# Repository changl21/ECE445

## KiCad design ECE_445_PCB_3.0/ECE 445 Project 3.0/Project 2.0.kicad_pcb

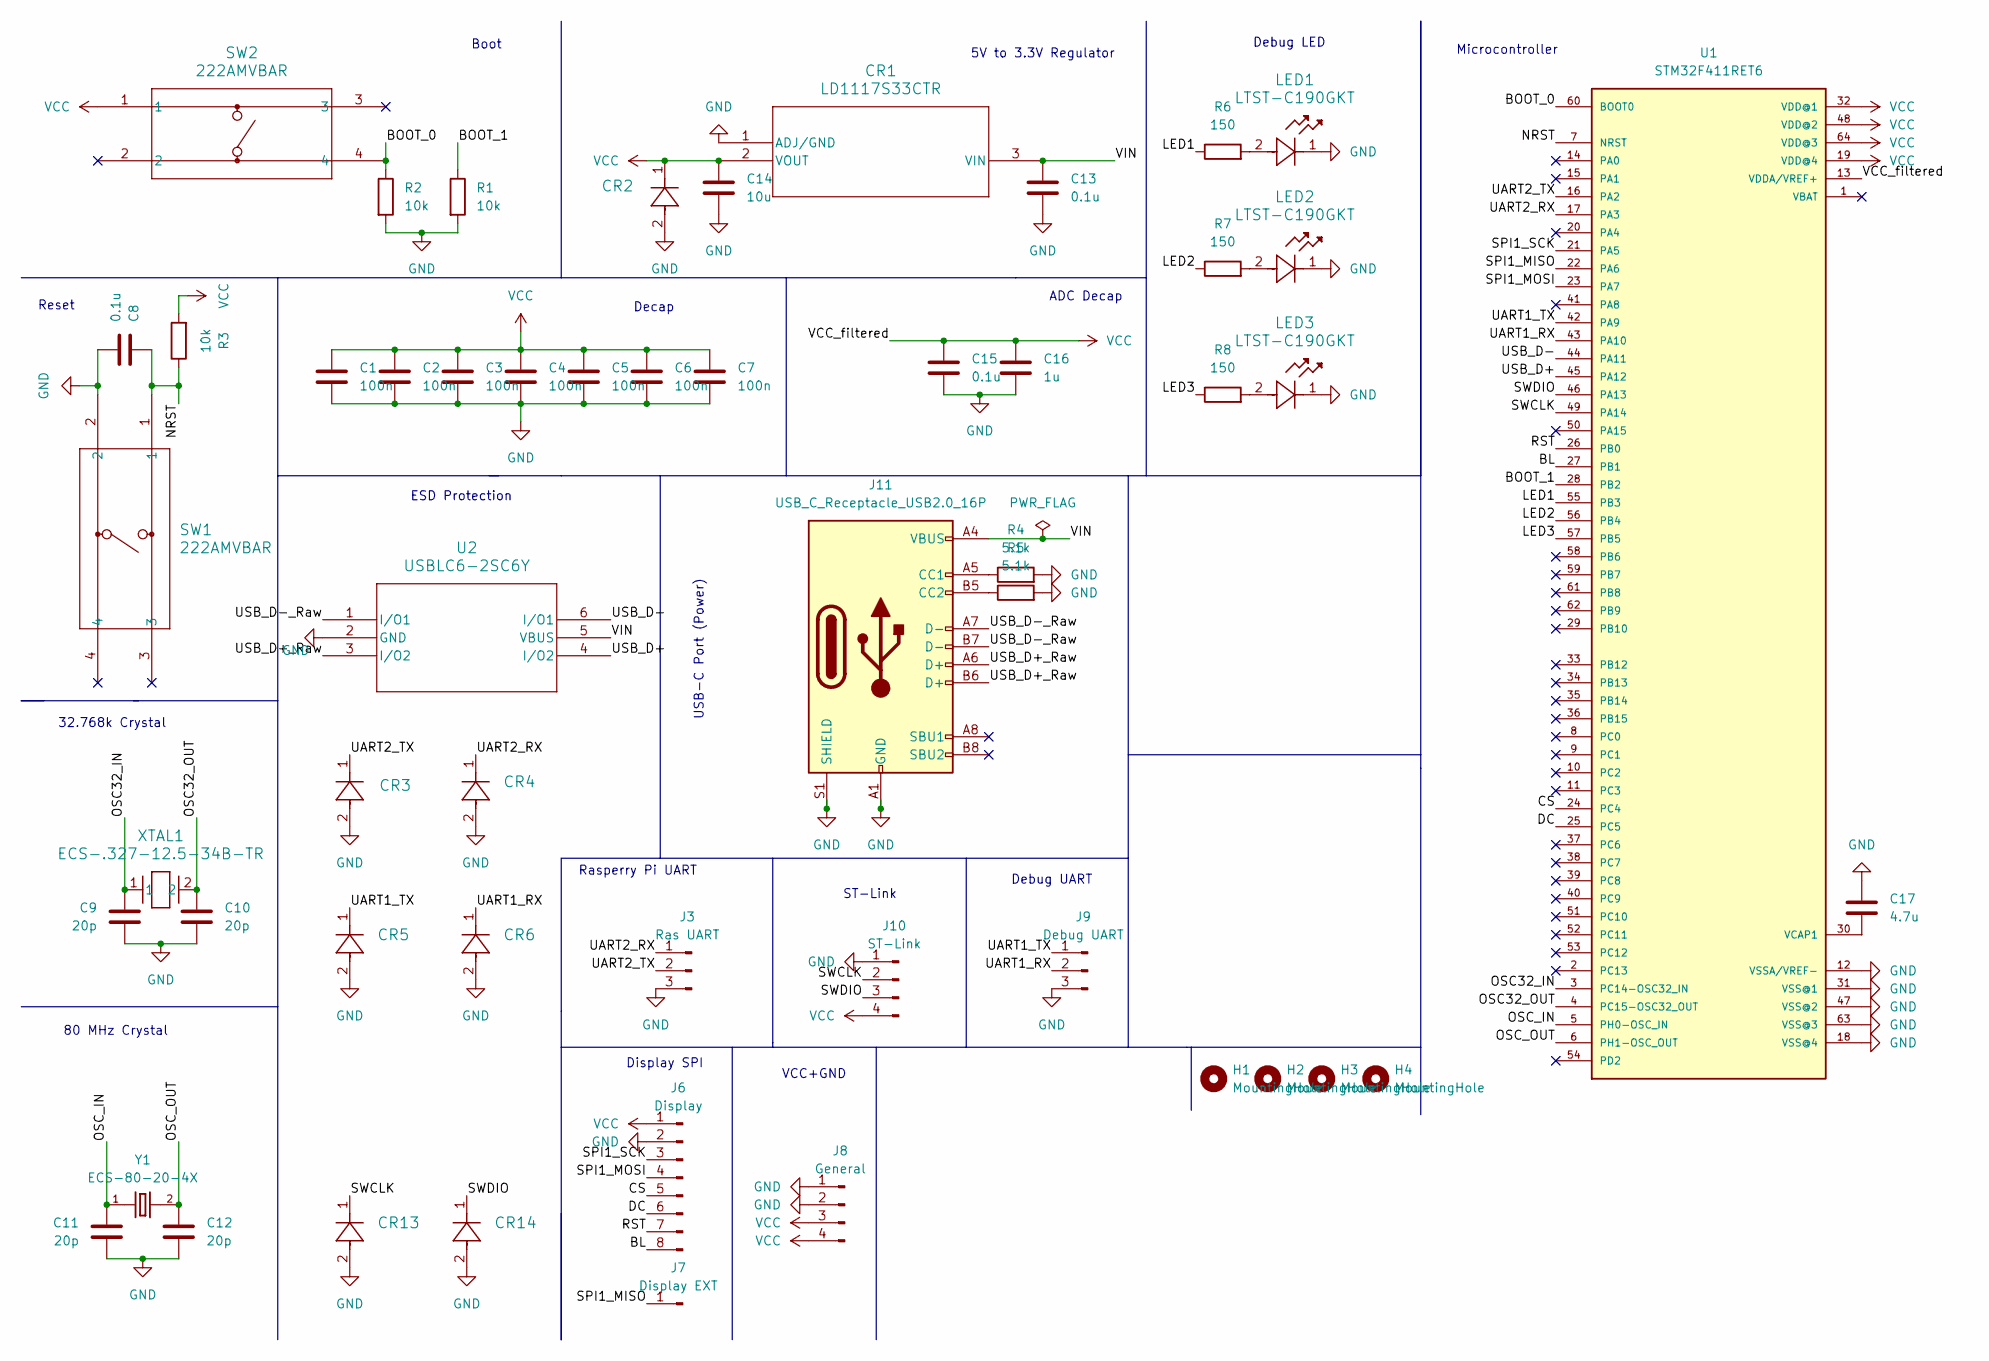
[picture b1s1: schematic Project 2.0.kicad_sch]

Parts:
C1, C2, C3, C4, C5, C6, C7: 100n; C_0603_1608Metric_Pad1.08x0.95mm_HandSolder
C8, C13, C15: 0.1u; C_0603_1608Metric_Pad1.08x0.95mm_HandSolder
C9, C10, C11, C12: 20p; C_0603_1608Metric_Pad1.08x0.95mm_HandSolder
C14: 10u; C_0805_2012Metric_Pad1.18x1.45mm_HandSolder
C16: 1u; C_0603_1608Metric_Pad1.08x0.95mm_HandSolder
C17: 4.7u; C_0603_1608Metric_Pad1.08x0.95mm_HandSolder
CR1: LD1117S33CTR; SOT-223_STM-L
CR2, CR3, CR4, CR5, CR6, CR13, CR14: PESD3V3L1BA_115; DIODE_PESD3V3L1BA_115_NEX-L
H1, H2, H3, H4: MountingHole; MountingHole_3.2mm_M3
J3: Ras UART; PinHeader_1x03_P2.54mm_Vertical
J6: Display; PinHeader_1x08_P2.54mm_Vertical
J7: Display EXT; PinHeader_1x01_P2.54mm_Vertical
J8: General; PinHeader_1x04_P2.54mm_Vertical
J9: Debug UART; PinHeader_1x03_P2.54mm_Vertical
J10: ST-Link; PinHeader_1x04_P2.54mm_Vertical
J11: USB_C_Receptacle_USB2.0_16P; USB_C_Receptacle_GCT_USB4105-xx-A_16P_TopMnt_Horizontal
LED1, LED2, LED3: LTST-C190GKT; LED_LTST-C190CKT_LTO
R1, R2, R3: 10k; R_0805_2012Metric_Pad1.20x1.40mm_HandSolder
R4, R5: 5.1k; R_0805_2012Metric_Pad1.20x1.40mm_HandSolder
R6, R7, R8: 150; R_0805_2012Metric_Pad1.20x1.40mm_HandSolder
SW1, SW2: 222AMVBAR; SO4_222A-M-V-B_CTS
U1: STM32F411RET6; QFP50P1200X1200X160-64N
U2: USBLC6-2SC6Y; SOT23-6L_STM-L
XTAL1: ECS-.327-12.5-34B-TR; XTAL_ECS-31B_ECS-L
Y1: ECS-80-20-4X; XTAL_ECS-80-20-4X

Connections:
/BL: J6.8, U1.27 (PB1)
/BOOT_0: R2.1, SW2.4, U1.60 (BOOT0)
/BOOT_1: R1.1, U1.28 (PB2)
/CS: J6.5, U1.24 (PC4)
/DC: J6.6, U1.25 (PC5)
/LED1: R6.1, U1.55 (PB3)
/LED2: R7.1, U1.56 (PB4)
/LED3: R8.1, U1.57 (PB5)
/NRST: C8.1, R3.1, SW1.1, U1.7 (NRST)
/OSC32_IN: C9.1, U1.3 (PC14-OSC32_IN), XTAL1.1
/OSC32_OUT: C10.1, U1.4 (PC15-OSC32_OUT), XTAL1.2
/OSC_IN: C11.1, U1.5 (PH0-OSC_IN), Y1.1
/OSC_OUT: C12.1, U1.6 (PH1-OSC_OUT), Y1.2
/RST: J6.7, U1.26 (PB0)
/SPI1_MISO: J7.1, U1.22 (PA6)
/SPI1_MOSI: J6.4, U1.23 (PA7)
/SPI1_SCK: J6.3, U1.21 (PA5)
/SWCLK: CR13.1, J10.2, U1.49 (PA14)
/SWDIO: CR14.1, J10.3, U1.46 (PA13)
/UART1_RX: CR6.1, J9.2, U1.43 (PA10)
/UART1_TX: CR5.1, J9.1, U1.42 (PA9)
/UART2_RX: CR4.1, J3.1, U1.17 (PA3)
/UART2_TX: CR3.1, J3.2, U1.16 (PA2)
/USB_D+: U1.45 (PA12), U2.4 (I/O2)
/USB_D+_Raw: J11.A6 (D+), J11.B6 (D+), U2.3 (I/O2)
/USB_D-: U1.44 (PA11), U2.6 (I/O1)
/USB_D-_Raw: J11.A7 (D-), J11.B7 (D-), U2.1 (I/O1)
/VIN: C13.1, CR1.3 (VIN), J11.A4 (VBUS), J11.A9 (VBUS), J11.B4 (VBUS), J11.B9 (VBUS), U2.5 (VBUS)
GND: C1.2, C2.2, C3.2, C4.2, C5.2, C6.2, C7.2, C8.2, C9.2, C10.2, C11.2, C12.2, C13.2, C14.2, C15.2, C16.2, C17.1, CR1.1 (ADJ/GND), CR2.2, CR3.2, CR4.2, CR5.2, CR6.2, CR13.2, CR14.2, J3.3, J6.2, J8.1, J8.2, J9.3, J10.1, J11.A1 (GND), J11.A12 (GND), J11.B1 (GND), J11.B12 (GND), J11.S1 (SHIELD), LED1.1, LED2.1, LED3.1, R1.2, R2.2, R4.2, R5.2, SW1.2, U1.12 (VSSA/VREF-), U1.18 (VSS@4), U1.31 (VSS@1), U1.47 (VSS@2), U1.63 (VSS@3), U2.2 (GND)
unnamed: J11.A5 (CC1), R4.1
unnamed: J11.B5 (CC2), R5.1
unnamed: LED1.2, R6.2
unnamed: LED2.2, R7.2
unnamed: LED3.2, R8.2
unnamed: C17.2, U1.30 (VCAP1)
VCC: C1.1, C2.1, C3.1, C4.1, C5.1, C6.1, C7.1, C14.1, C15.1, C16.1, CR1.2 (VOUT), CR2.1, J6.1, J8.3, J8.4, J10.4, R3.2, SW2.1, U1.13 (VDDA/VREF+), U1.19 (VDD@4), U1.32 (VDD@1), U1.48 (VDD@2), U1.64 (VDD@3)

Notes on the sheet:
Microcontroller
Rasperry Pi UART
Boot
Debug LED
32.768k Crystal
Reset
Debug UART
USB-C Port (Power)
ADC Decap
VCC+GND
Display SPI
Decap
ST-Link
ESD Protection
5V to 3.3V Regulator
80 MHz Crystal

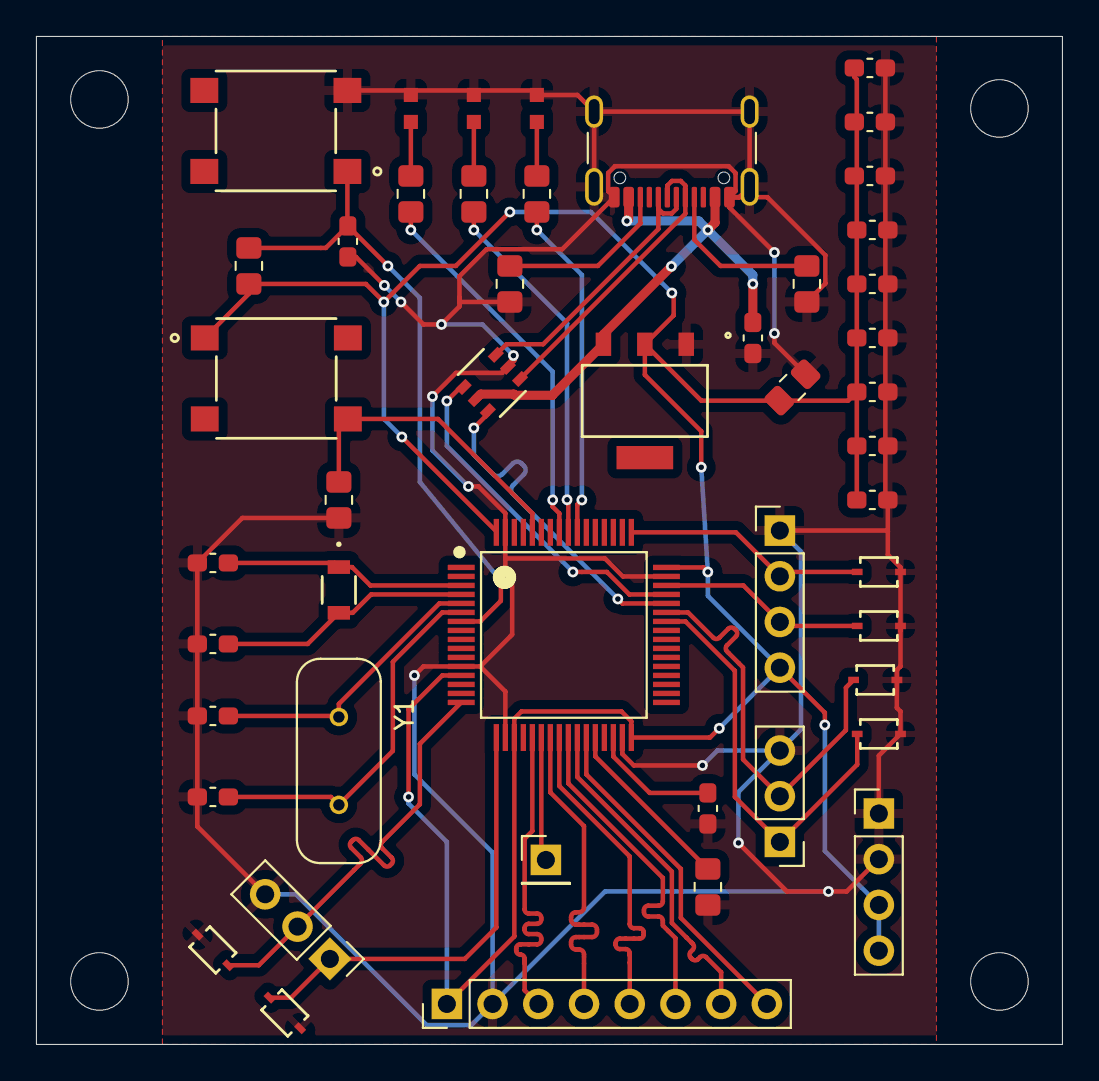
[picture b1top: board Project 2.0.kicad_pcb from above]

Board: 2 copper layers, 57.0 x 56.0 mm, 52 parts (0 on the bottom side), 36 nets.

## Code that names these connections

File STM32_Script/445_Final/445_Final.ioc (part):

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Mcu.Name=STM32F411R(C-E)Tx
Mcu.Package=LQFP64
Mcu.UserName=STM32F411RETx
PA10.Mode=Asynchronous
PA10.Signal=USART1_RX
PA13.GPIOParameters=GPIO_Label
PA13.GPIO_Label=TMS
PA13.Mode=Serial_Wire
PA13.Signal=SYS_JTMS-SWDIO
PA14.GPIOParameters=GPIO_Label
PA14.GPIO_Label=TCK
PA14.Mode=Serial_Wire
PA14.Signal=SYS_JTCK-SWCLK
PA2.GPIOParameters=GPIO_Label
PA2.GPIO_Label=USART_TX
PA2.Mode=Asynchronous
PA2.Signal=USART2_TX
PA3.GPIOParameters=GPIO_Label
PA3.GPIO_Label=USART_RX
PA3.Mode=Asynchronous
PA3.Signal=USART2_RX
PA5.Mode=Simplex_Bidirectional_Master
PA5.Signal=SPI1_SCK
PA7.Mode=Simplex_Bidirectional_Master
PA7.Signal=SPI1_MOSI
PA9.Mode=Asynchronous
PA9.Signal=USART1_TX
PB0.Signal=GPIO_Output
PB1.Signal=GPIO_Output
PB3.GPIOParameters=GPIO_Label
PB3.GPIO_Label=SWO
PB3.Signal=SYS_JTDO-SWO
PC13-ANTI_TAMP.GPIOParameters=GPIO_Label,GPIO_ModeDefaultEXTI
PC13-ANTI_TAMP.GPIO_Label=B1 [Blue PushButton]
PC13-ANTI_TAMP.GPIO_ModeDefaultEXTI=GPIO_MODE_IT_FALLING
PC13-ANTI_TAMP.Signal=GPXTI13
PC14-OSC32_IN.Mode=LSE-External-Oscillator
PC14-OSC32_IN.Signal=RCC_OSC32_IN
PC15-OSC32_OUT.Mode=LSE-External-Oscillator
PC15-OSC32_OUT.Signal=RCC_OSC32_OUT
PC4.Signal=GPIO_Output
PC5.Signal=GPIO_Output
PH0\ -\ OSC_IN.Mode=HSE-External-Clock-Source
PH0\ -\ OSC_IN.Signal=RCC_OSC_IN
PH1\ -\ OSC_OUT.Mode=HSE-External-Clock-Source
PH1\ -\ OSC_OUT.Signal=RCC_OSC_OUT
RCC.HSE_VALUE=8000000
RCC.SYSCLKFreq_VALUE=84000000
RCC.SYSCLKSource=RCC_SYSCLKSOURCE_PLLCLK
board=NUCLEO-F411RE
boardIOC=true

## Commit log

2025-05-08 stm32
2025-05-08 upload notebook
2025-05-08 added video
2025-05-08 modified week 8
2025-05-08 Chang
2025-05-13 Update Week 1
2025-05-14 Update All Weeks!
2025-05-14 Update More
2025-05-14 Update!
2025-05-14 final update
2025-05-14 Block
2025-05-14 revised readme
